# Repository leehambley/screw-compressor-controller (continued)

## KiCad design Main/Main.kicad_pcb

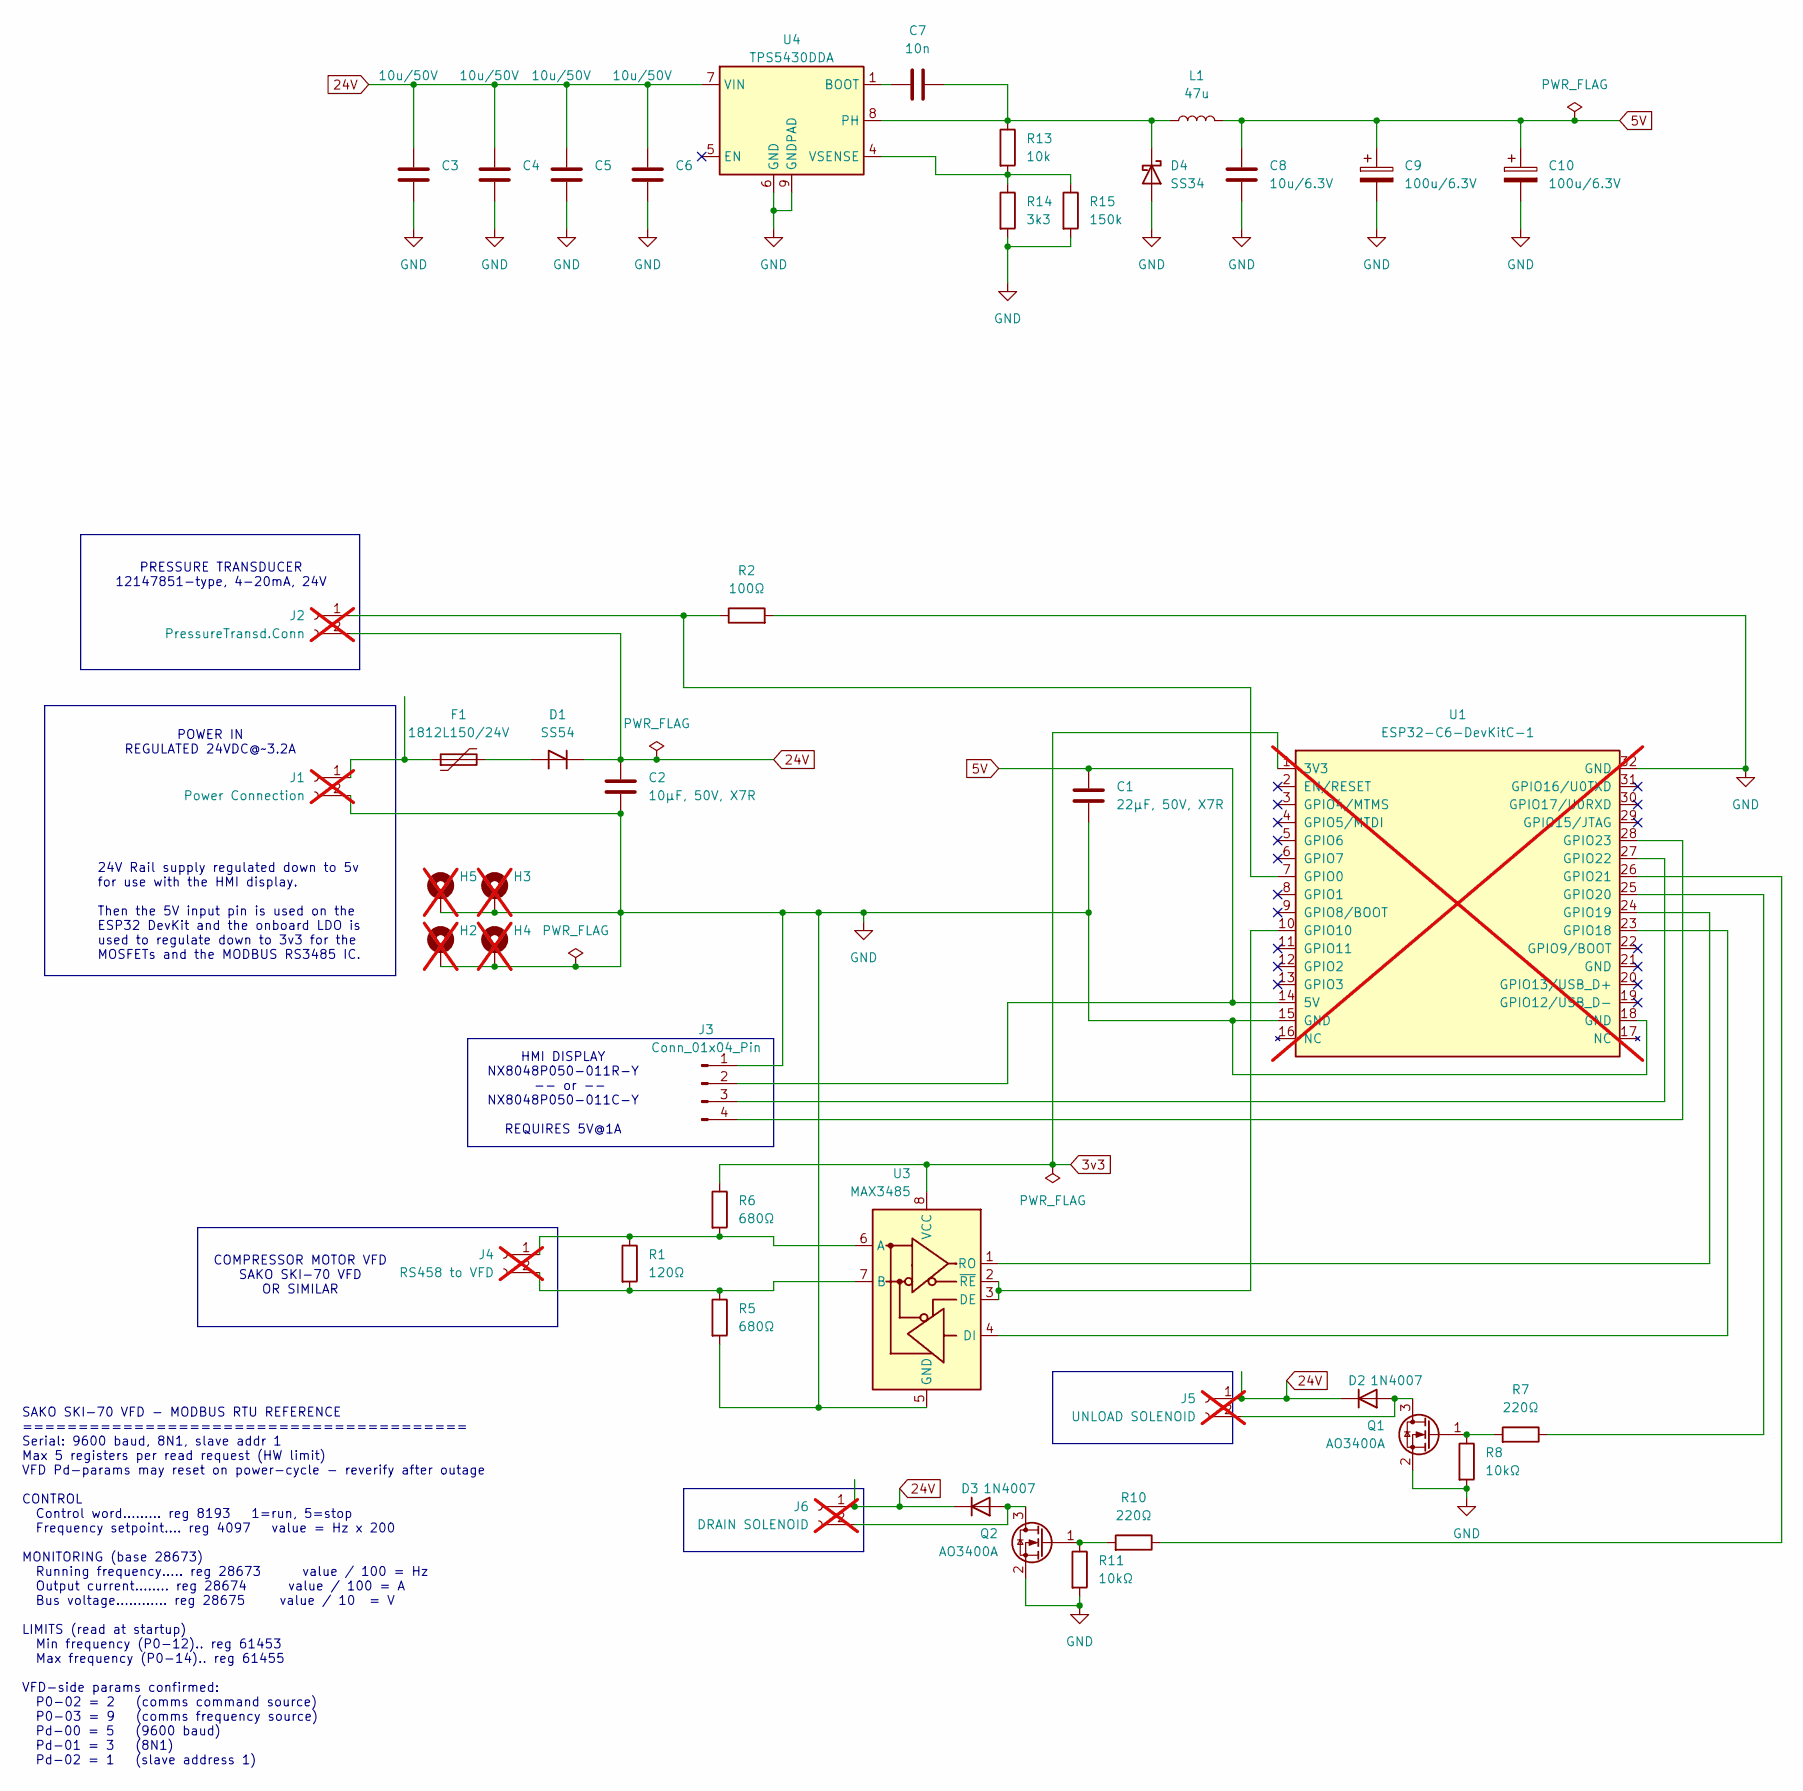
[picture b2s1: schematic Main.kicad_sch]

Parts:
C1: 22µF, 50V, X7R; C_0603_1608Metric; LCSC C14663
C2: 10µF, 50V, X7R; C_1206_3216Metric; LCSC C49326770
C3, C4, C5, C6: 10u/50V; C_1206_3216Metric; MPN CL31A106KBHNNNE; LCSC C13585
C7: 10n; C_0402_1005Metric; MPN CL05B103KB5NNNC; LCSC C15195
C8: 10u/6.3V; C_0402_1005Metric; MPN CL05A106MQ5NUNC; LCSC C15525
C9, C10: 100u/6.3V; CP_EIA-3528-21_Kemet-B; MPN TAJB107K006RNJ; LCSC C16133
D1: SS54; D_SMA; LCSC C22452
D2, D3: 1N4007; D_DO-41_SOD81_P10.16mm_Horizontal; LCSC C84641
D4: SS34; D_SMA; MPN SS34; LCSC C8678
F1: 1812L150/24V; Fuse_1812_4532Metric; LCSC C49318453
H2, H3, H4, H5: MountingHole_Pad_MP; MountingHole_3.2mm_M3_DIN965_Pad; not fitted
J1: Power Connection; TerminalBlock_MaiXu_MX126-5.0-02P_1x02_P5.00mm; LCSC C3703; not fitted
J2: PressureTransd.Conn; TerminalBlock_MaiXu_MX126-5.0-02P_1x02_P5.00mm; LCSC C3703; not fitted
J3: Conn_01x04_Pin; PinHeader_1x04_P2.54mm_Horizontal
J4: RS458 to VFD; TerminalBlock_MaiXu_MX126-5.0-02P_1x02_P5.00mm; LCSC C3703; not fitted
J5: UNLOAD SOLENOID; TerminalBlock_MaiXu_MX126-5.0-02P_1x02_P5.00mm; LCSC C3703; not fitted
J6: DRAIN SOLENOID; TerminalBlock_MaiXu_MX126-5.0-02P_1x02_P5.00mm; LCSC C3703; not fitted
L1: 47u; L_Wuerth_HCM-1190; MPN MWSA1004S-470MT; LCSC C408491
Q1, Q2: AO3400A; SOT-23; LCSC C20917
R1: 120Ω; R_0805_2012Metric; LCSC C17437
R2: 100Ω; R_0805_2012Metric; LCSC C17408
R5, R6: 680Ω; R_0805_2012Metric; LCSC C17798
R7, R10: 220Ω; R_0805_2012Metric; LCSC C17557
R8, R11: 10kΩ; R_0805_2012Metric; LCSC C17414
R13: 10k; R_0402_1005Metric; MPN 0402WGF1002TCE; LCSC C25744
R14: 3k3; R_0402_1005Metric; MPN 0402WGF3301TCE; LCSC C25890
R15: 150k; R_0402_1005Metric; MPN 0402WGF1503TCE; LCSC C25755
U1: ESP32-C6-DevKitC-1; not fitted
U3: MAX3485; SOIC-8_3.9x4.9mm_P1.27mm
U4: TPS5430DDA; TI_SO-PowerPAD-8_ThermalVias; MPN TPS5430DDAR; JLC LSOP-8_EP_3.9x4.9x1.27P

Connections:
3v3: R6.1, U1.1 (3V3), U3.8 (VCC)
5V: C1.1, C8.1, C9.1, C10.1, J3.2, L1.2, U1.14 (5V)
24V: C2.1, C3.1, C4.1, C5.1, C6.1, D1.1 (K), D2.1 (K), D3.1 (K), J2.2, J5.1, J6.1, U4.7 (VIN)
GND: C1.2, C2.2, C3.2, C4.2, C5.2, C6.2, C8.2, C9.2, C10.2, D4.2 (A), H2.MP, H3.MP, H4.MP, H5.MP, J1.2, J3.1, Q1.2 (S), Q2.2 (S), R2.2, R5.2, R8.2, R11.2, R14.2, R15.2, U1.15 (GND), U1.18 (GND), U1.32 (GND), U3.5 (GND), U4.6 (GND), U4.9 (GNDPAD)
unnamed: D1.2 (A), F1.2
unnamed: D2.2 (A), J5.2, Q1.3 (D)
unnamed: D3.2 (A), J6.2, Q2.3 (D)
unnamed: C7.2, D4.1 (K), L1.1, R13.1, U4.8 (PH)
unnamed: F1.1, J1.1
unnamed: J2.1, R2.1, U1.7 (GPIO0)
unnamed: J3.3, U1.27 (GPIO22)
unnamed: J3.4, U1.28 (GPIO23)
unnamed: J4.1, R1.1, R6.2, U3.6 (A)
unnamed: J4.2, R1.2, R5.1, U3.7 (B)
unnamed: Q1.1 (G), R7.2, R8.1
unnamed: Q2.1 (G), R10.2, R11.1
unnamed: U1.10 (GPIO10), U3.2 (~RE), U3.3 (DE)
unnamed: U1.23 (GPIO18), U3.4 (DI)
unnamed: U1.24 (GPIO19), U3.1 (RO)
unnamed: R7.1, U1.25 (GPIO20)
unnamed: R10.1, U1.26 (GPIO21)
unnamed: C7.1, U4.1 (BOOT)
unnamed: R13.2, R14.1, R15.1, U4.4 (VSENSE)

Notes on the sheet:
24V Rail supply regulated down to 5v for use with the HMI display. Then the 5V input pin is used on the ESP32 DevKit and the onboard LDO is used to regulate down to 3v3 for the MOSFETs and the MODBUS RS3485 IC.
HMI DISPLAY NX8048P050-011R-Y -- or -- NX8048P050-011C-Y REQUIRES 5V@1A
POWER IN REGULATED 24VDC@~3.2A
SAKO SKI-70 VFD - MODBUS RTU REFERENCE ======================================== Serial: 9600 baud, 8N1, slave addr 1 Max 5 registers per read request (HW limit) VFD Pd-params may reset on power-cycle - reverify after outage CONTROL Control word......... reg 8193 1=run, 5=stop Frequency setpoint....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
PRESSURE TRANSDUCER 12147851-type, 4-20mA, 24V
COMPRESSOR MOTOR VFD SAKO SKI-70 VFD OR SIMILAR

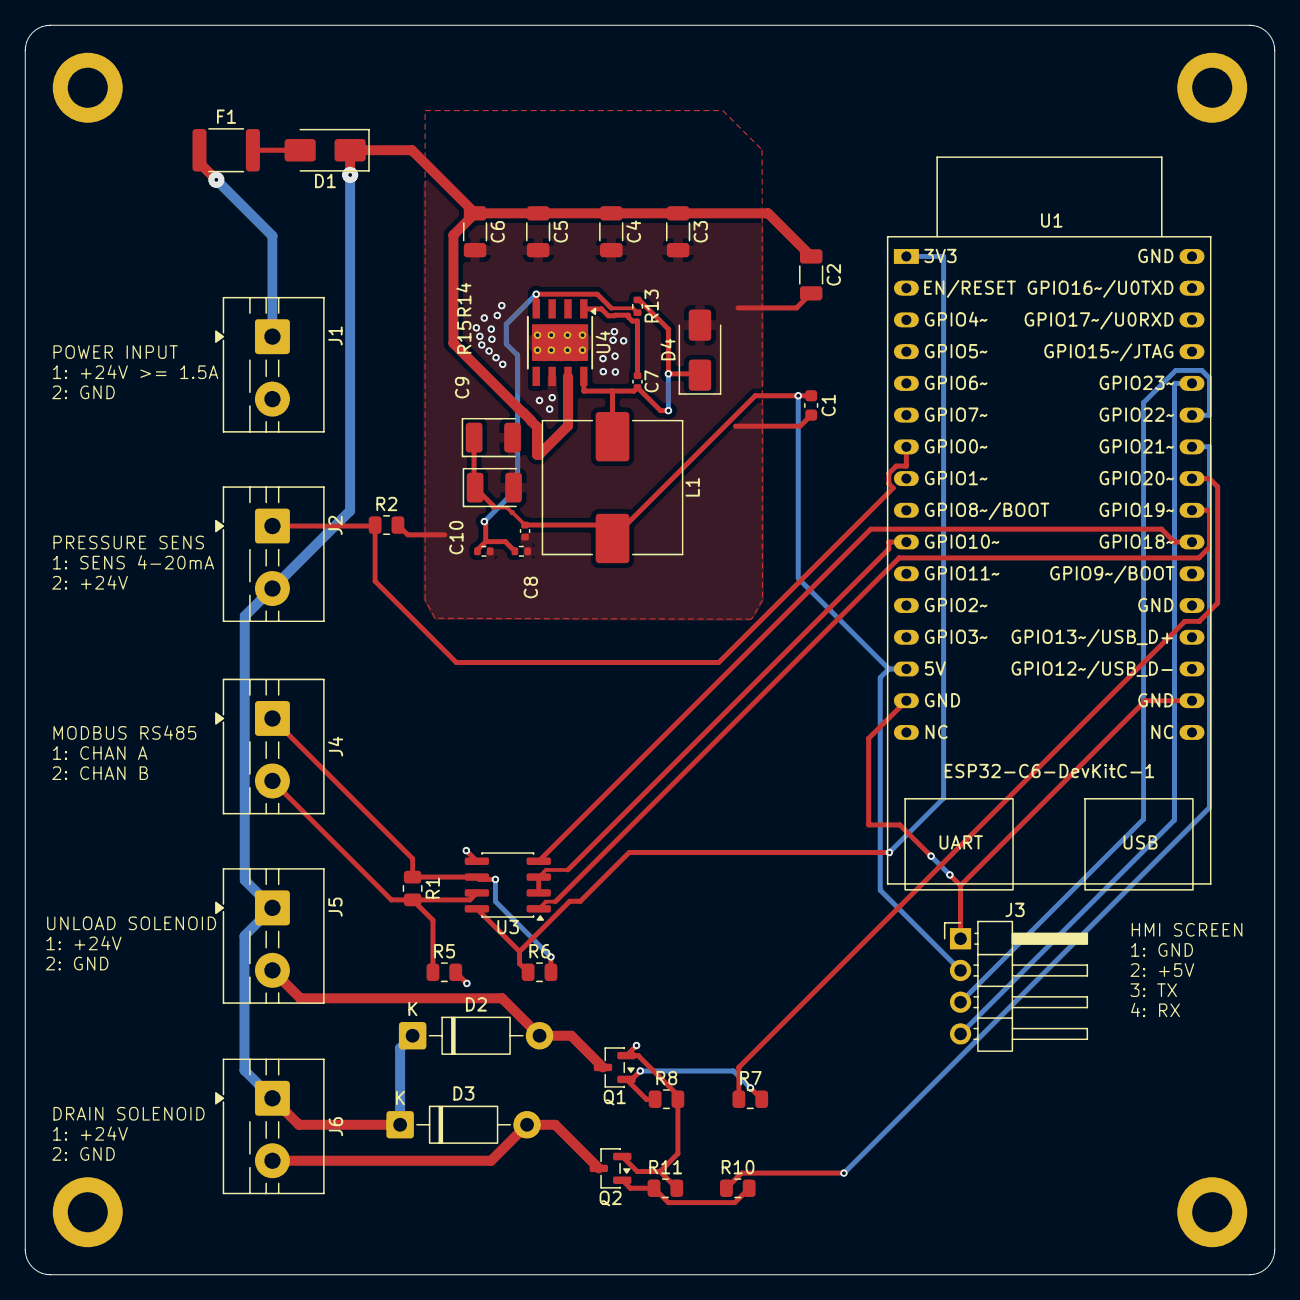
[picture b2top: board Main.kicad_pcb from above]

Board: 2 copper layers, 100.0 x 100.0 mm, 42 parts (0 on the bottom side), 23 nets.

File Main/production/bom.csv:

Designator,Footprint,Quantity,Value,LCSC Part #
C1,0603,1,"22µF, 50V, X7R",C14663
"C10, C9",CP_EIA-3528-21_Kemet-B,2,100u/6.3V,C16133
C2,1206,1,"10µF, 50V, X7R",C49326770
"C3, C4, C5, C6",1206,4,10u/50V,C13585
C7,0402,1,10n,C15195
C8,0402,1,10u/6.3V,C15525
D1,D_SMA,1,SS54,C22452
"D2, D3",D_DO-41_SOD81_P10.16mm_Horizontal,2,1N4007,C84641
D4,D_SMA,1,SS34,C8678
F1,1812,1,1812L150/24V,C49318453
J1,TerminalBlock_MaiXu_MX126-5.0-02P_1x02_P5.00mm,1,Power Connection,C3703
J2,TerminalBlock_MaiXu_MX126-5.0-02P_1x02_P5.00mm,1,PressureTransd.Conn,C3703
J3,PinHeader_1x04_P2.54mm_Horizontal,1,Conn_01x04_Pin,
J4,TerminalBlock_MaiXu_MX126-5.0-02P_1x02_P5.00mm,1,RS458 to VFD,C3703
J5,TerminalBlock_MaiXu_MX126-5.0-02P_1x02_P5.00mm,1,UNLOAD SOLENOID,C3703
J6,TerminalBlock_MaiXu_MX126-5.0-02P_1x02_P5.00mm,1,DRAIN SOLENOID,C3703
L1,L_Wuerth_HCM-1190,1,47u,C408491
"Q1, Q2",SOT-23,2,AO3400A,C20917
R1,0805,1,120Ω,C17437
"R10, R7",0805,2,220Ω,C17557
"R11, R8",0805,2,10kΩ,C17414
R13,0402,1,10k,C25744
R14,0402,1,3k3,C25890
R15,0402,1,150k,C25755
R2,0805,1,100Ω,C17408
"R5, R6",0805,2,680Ω,C17798
U3,SOIC-8_3.9x4.9mm_P1.27mm,1,MAX3485,
U4,TI_SO-PowerPAD-8_ThermalVias,1,TPS5430DDA,C9864

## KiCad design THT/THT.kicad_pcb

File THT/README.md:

# THT controller board (rev A)

A 100 × 100 mm, 2-layer through-hole version of the breadboard controller,
for hand soldering. There is no schematic: [gen_board.py](gen_board.py) declares
every part, position and net, and is the source of truth.

## Ordering (JLCPCB)

Upload `production/THT-gerbers-JLCPCB.zip`. Defaults are fine: 2 layers,
1.6 mm, HASL, 1 oz copper. Parts list: `production/BOM.csv`.

## Rebuilding

```sh
PY=/Applications/KiCad/KiCad.app/Contents/Frameworks/Python.framework/Versions/Current/bin/python3
$PY gen_board.py   # parts + nets, unrouted
$PY route.py       # Freerouting (needs Homebrew openjdk@25) + GND pours
```

Then re-export:

```sh
K=/Applications/KiCad/KiCad.app/Contents/MacOS/kicad-cli
rm -rf production/gerbers && mkdir -p production/gerbers
$K pcb drc -o build/drc.txt THT.kicad_pcb
$K pcb export gerbers --layers F.Cu,B.Cu,F.SilkS,B.SilkS,F.Mask,B.Mask,Edge.Cuts --no-protel-ext -o production/gerbers/ THT.kicad_pcb
$K pcb export drill --format excellon --excellon-separate-th -o production/gerbers/ THT.kicad_pcb
(cd production/gerbers && rm -f ../THT-gerbers-JLCPCB.zip && zip -q ../THT-gerbers-JLCPCB.zip *)
```

## Circuit

| Block | Parts | Notes |
|---|---|---|
| 24 V in | J1, F1 (2 A slow 5×20), D1 1N5822, C1, C2 | D1 = reverse-polarity protection |
| 5 V | U2 LM2596T-5.0, L1 33 µH, D2 1N5822, C3, C4 | feeds Nextion directly, DevKit 5V pin via D3 1N5819 (no back-feed into USB) |
| 3V3 | DevKit's own regulator | MAX3485, NTC pull-ups, ADC clamp |
| Valve 1 (start-assist, GPIO20) | Q1 IRLZ34N, R10 100R gate, R12 100k pull-down, D4 1N5819, LED2 | |
| Valve 2 (drain, GPIO21) | Q2, R11, R13, D5, LED3 | |
| Pressure 4–20 mA (GPIO0) | J4, R20 100R shunt, R21 1k + C20 100nF, D20 BAT85 clamp | J4: top = +24 V loop supply, bottom = signal |
| NTC1 rotor (GPIO1), NTC2 motor (GPIO2), NTC3 rotor 2 (GPIO3) | 10k pull-up, 1k + 100nF each | probes are non-polar |
| RS485 (GPIO18 DI, GPIO19 RO, GPIO10 DE/RE) | U3 MAX3485 (DIP-8, socketed), R40 120R via JP1, R42 10k RO pull-up | J8: A, B, GND |
| Nextion (GPIO22 RX, GPIO23 TX) | J9 JST XH 4-pin (B4B-XH-A): 5V, TX, RX, GND | same connector and pin order as the display end |

Bottom layer is an almost unbroken ground plane, top is ground-poured too.
Valve current returns along the right-hand side to J1; the analog front
end is on the far left, away from it. That is the lesson from the
breadboard, whose readings were wrecked by a shared, poorly soldered ground.

Flyback diodes are Schottky (1N5819), so the valve PWM hold can go well
above 1 kHz (quiet) without the 1N400x reverse-recovery heating.

## Check before ordering parts

- F1 clips: footprint is Littelfuse 100-series clips, 20.5 mm pitch. Buy
  matching clips or swap the footprint for your holder.
- L1: 12 mm radial, 5 mm lead pitch, ≥ 1.5 A.
- U2: footprint is for the staggered-lead TO-220-5 (LM2596T-5.0 /
  "flow LB03"); straight-lead parts can be bent to fit.
- DevKit goes in 2× 1x16 female headers; its USB ports overhang the bottom
  edge so it can still be flashed in place.

## Firmware follow-ups

- NTC2 (GPIO2) and NTC3 (GPIO3) are new; the firmware only reads GPIO1.

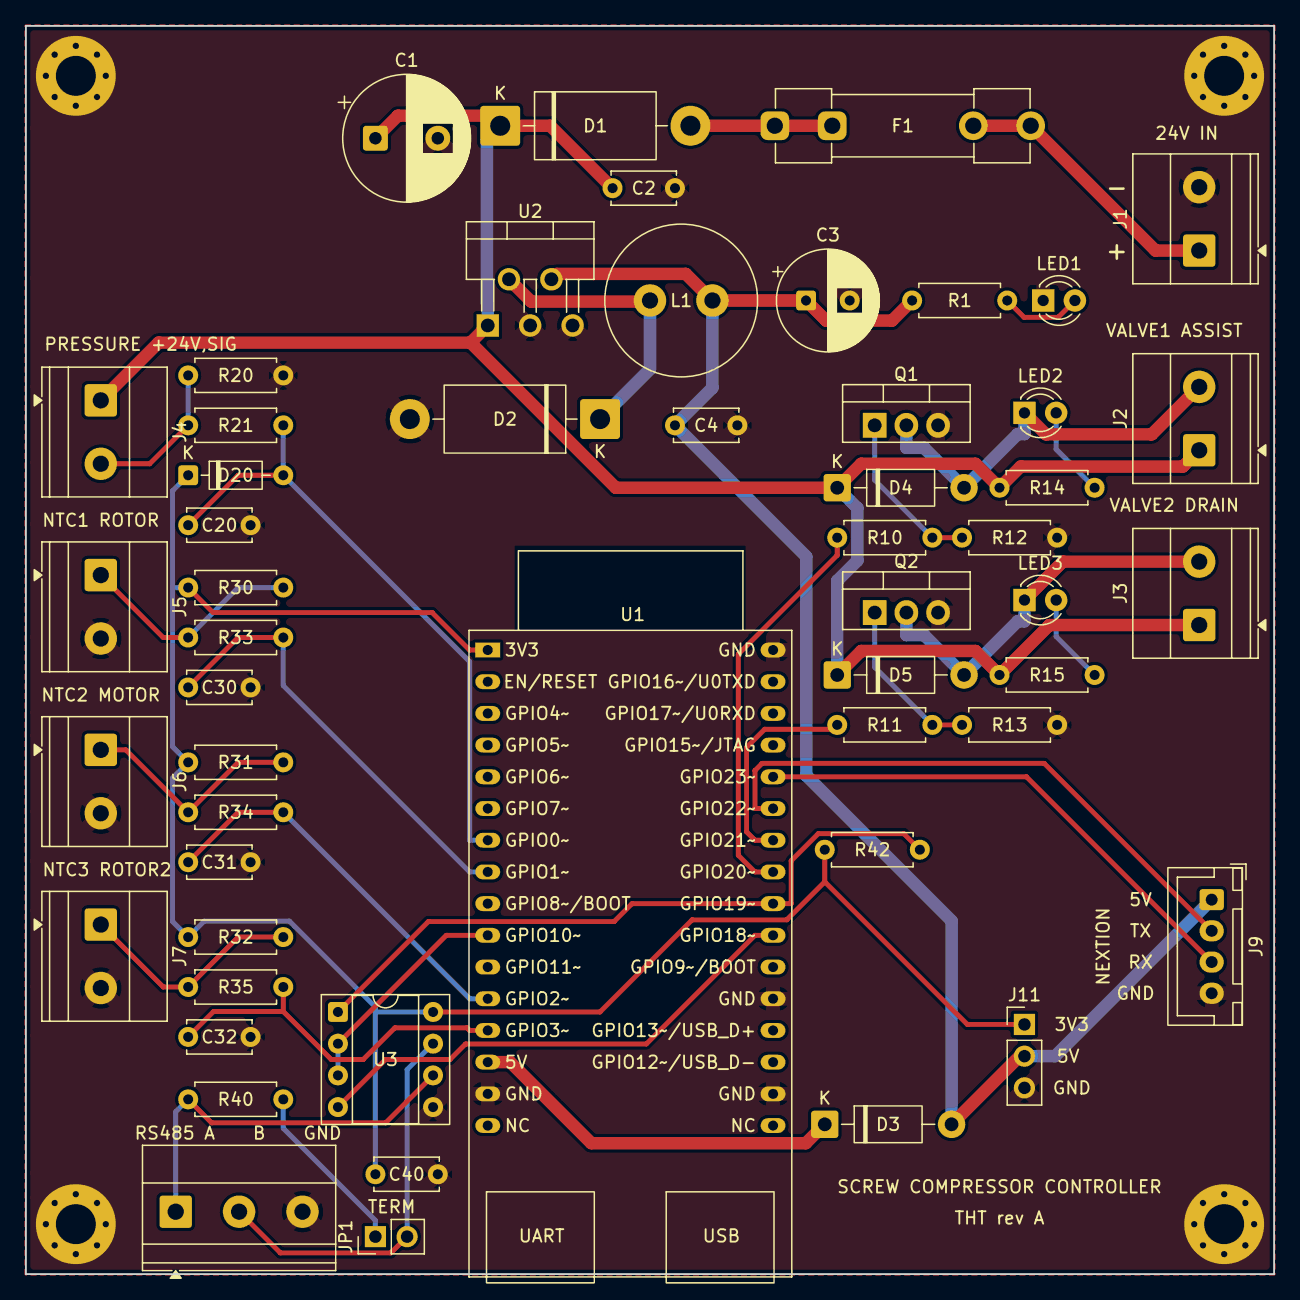
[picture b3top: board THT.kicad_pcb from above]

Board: 2 copper layers, 100.0 x 100.0 mm, 57 parts (0 on the bottom side), 33 nets.

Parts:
C1: 220uF 50V; CP_Radial_D10.0mm_P5.00mm
C2: 100nF 50V; C_Disc_D5.0mm_W2.5mm_P5.00mm
C3: 220uF 25V low-ESR; CP_Radial_D8.0mm_P3.50mm
C4, C20, C30, C31, C32, C40: 100nF; C_Disc_D5.0mm_W2.5mm_P5.00mm
D1, D2: 1N5822; D_DO-201AD_P15.24mm_Horizontal
D3, D4, D5: 1N5819; D_DO-41_SOD81_P10.16mm_Horizontal
D20: BAT85; D_DO-35_SOD27_P7.62mm_Horizontal
F1: 2A slow 5x20; Fuseholder_Clip-5x20mm_Littelfuse_100_Inline_P20.50x4.60mm_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
H1, H2, H3, H4: M3; MountingHole_3.2mm_M3_Pad_Via
J1: 24V IN; TerminalBlock_Phoenix_MKDS-1,5-2-5.08_1x02_P5.08mm_Horizont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
J2: VALVE1; TerminalBlock_Phoenix_MKDS-1,5-2-5.08_1x02_P5.08mm_Horizont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
J3: VALVE2; TerminalBlock_Phoenix_MKDS-1,5-2-5.08_1x02_P5.08mm_Horizont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
J4: PRESSURE; TerminalBlock_Phoenix_MKDS-1,5-2-5.08_1x02_P5.08mm_Horizont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
J5: NTC1; TerminalBlock_Phoenix_MKDS-1,5-2-5.08_1x02_P5.08mm_Horizont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
J6: NTC2; TerminalBlock_Phoenix_MKDS-1,5-2-5.08_1x02_P5.08mm_Horizont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
J7: NTC3; TerminalBlock_Phoenix_MKDS-1,5-2-5.08_1x02_P5.08mm_Horizont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
J8: RS485; TerminalBlock_Phoenix_MKDS-1,5-3-5.08_1x03_P5.08mm_Horizont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
J9: JST XH 4P (B4B-XH-A); JST_XH_B4B-XH-A_1x04_P2.50mm_Vertical
J11: TEST; PinHeader_1x03_P2.54mm_Vertical
JP1: TERM; PinHeader_1x02_P2.54mm_Vertical
L1: 33uH 3A; L_Radial_D12.0mm_P5.00mm_Fastron_11P
LED1: green 3mm; LED_D3.0mm
LED2, LED3: red 3mm; LED_D3.0mm
Q1, Q2: IRLZ34N; TO-220-3_Vertical
R1, R21, R33, R34, R35: 1k; R_Axial_DIN0207_L6.3mm_D2.5mm_P7.62mm_Horizontal
R10, R11: 100R; R_Axial_DIN0207_L6.3mm_D2.5mm_P7.62mm_Horizontal
R12, R13: 100k; R_Axial_DIN0207_L6.3mm_D2.5mm_P7.62mm_Horizontal
R14, R15: 4k7; R_Axial_DIN0207_L6.3mm_D2.5mm_P7.62mm_Horizontal
R20: 100R 1%; R_Axial_DIN0207_L6.3mm_D2.5mm_P7.62mm_Horizontal
R30, R31, R32: 10k 1%; R_Axial_DIN0207_L6.3mm_D2.5mm_P7.62mm_Horizontal
R40: 120R; R_Axial_DIN0207_L6.3mm_D2.5mm_P7.62mm_Horizontal
R42: 10k; R_Axial_DIN0207_L6.3mm_D2.5mm_P7.62mm_Horizontal
U1: ESP32-C6-DevKitC-1
U2: LM2596T-5.0; TO-220-5_P3.4x3.7mm_StaggerOdd_Lead3.8mm_Vertical
U3: MAX3485CPA; DIP-8_W7.62mm_Socket

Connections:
5V_DK: D3.1, U1.14
+3V3: C40.1, D20.1, J11.1, R30.1, R31.1, R32.1, R42.1, U1.1, U3.8
+5V: C3.1, C4.1, D3.2, J9.1, J11.2, L1.2, R1.1, U2.4
+24V: C1.1, C2.1, D1.1, D4.1, D5.1, J2.1, J3.1, J4.1, R14.1, R15.1, U2.1
ADC0: C20.1, D20.2, R21.2, U1.7
ADC1: C30.1, R33.2, U1.8
ADC2: C31.1, R34.2, U1.12
ADC3: C32.1, R35.2, U1.13
DRAIN1: D4.2, J2.2, LED2.1, Q1.2
DRAIN2: D5.2, J3.2, LED3.1, Q2.2
G1: Q1.1, R10.2, R12.1
G2: Q2.1, R11.2, R13.1
GND: C1.2, C2.2, C3.2, C4.2, C20.2, C30.2, C31.2, C32.2, C40.2, D2.2, H1.1, H2.1, H3.1, H4.1, J1.2, J5.2, J6.2, J7.2, J8.3, J9.4, J11.3, LED1.1, Q1.3, Q2.3, R12.2, R13.2, R20.2, U1.15, U1.18, U1.21, U1.32, U2.3, U2.5, U3.5
LED_PWR: LED1.2, R1.2
LED_V1: LED2.2, R14.2
LED_V2: LED3.2, R15.2
LOOP: J4.2, R20.1, R21.1
MB_DE: U1.10, U3.2, U3.3
MB_DI: U1.23, U3.4
MB_RO: R42.2, U1.24, U3.1
NEX_RX: J9.3, U1.28
NEX_TX: J9.2, U1.27
NTC1: J5.1, R30.2, R33.1
NTC2: J6.1, R31.2, R34.1
NTC3: J7.1, R32.2, R35.1
RS_A: J8.1, R40.1, U3.6
RS_B: J8.2, JP1.2, U3.7
SW: D2.1, L1.1, U2.2
TERM: JP1.1, R40.2
V1_IN: R10.1, U1.25
V2_IN: R11.1, U1.26
VIN_F: D1.2, F1.1
VIN_RAW: F1.2, J1.1

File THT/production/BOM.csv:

Qty,References,Value,Footprint
1,C1,220uF 50V,CP_Radial_D10.0mm_P5.00mm
1,C2,100nF 50V,C_Disc_D5.0mm_W2.5mm_P5.00mm
1,C3,220uF 25V low-ESR,CP_Radial_D8.0mm_P3.50mm
6,C4 C20 C30 C31 C32 C40,100nF,C_Disc_D5.0mm_W2.5mm_P5.00mm
2,D1 D2,1N5822,D_DO-201AD_P15.24mm_Horizontal
3,D3 D4 D5,1N5819,D_DO-41_SOD81_P10.16mm_Horizontal
1,D20,BAT85,D_DO-35_SOD27_P7.62mm_Horizontal
1,F1,2A slow 5x20,Fuseholder_Clip-5x20mm_Littelfuse_100_Inline_P20.50x4.60mm_D1.30mm_Horizontal
1,J1,24V IN,"TerminalBlock_Phoenix_MKDS-1,5-2-5.08_1x02_P5.08mm_Horizontal"
1,J2,VALVE1,"TerminalBlock_Phoenix_MKDS-1,5-2-5.08_1x02_P5.08mm_Horizontal"
1,J3,VALVE2,"TerminalBlock_Phoenix_MKDS-1,5-2-5.08_1x02_P5.08mm_Horizontal"
1,J4,PRESSURE,"TerminalBlock_Phoenix_MKDS-1,5-2-5.08_1x02_P5.08mm_Horizontal"
1,J5,NTC1,"TerminalBlock_Phoenix_MKDS-1,5-2-5.08_1x02_P5.08mm_Horizontal"
1,J6,NTC2,"TerminalBlock_Phoenix_MKDS-1,5-2-5.08_1x02_P5.08mm_Horizontal"
1,J7,NTC3,"TerminalBlock_Phoenix_MKDS-1,5-2-5.08_1x02_P5.08mm_Horizontal"
1,J8,RS485,"TerminalBlock_Phoenix_MKDS-1,5-3-5.08_1x03_P5.08mm_Horizontal"
1,J9,JST XH 4P (B4B-XH-A),JST_XH_B4B-XH-A_1x04_P2.50mm_Vertical
1,J11,TEST,PinHeader_1x03_P2.54mm_Vertical
1,JP1,TERM,PinHeader_1x02_P2.54mm_Vertical
1,L1,33uH 3A,L_Radial_D12.0mm_P5.00mm_Fastron_11P
1,LED1,green 3mm,LED_D3.0mm
2,LED2 LED3,red 3mm,LED_D3.0mm
2,Q1 Q2,IRLZ34N,TO-220-3_Vertical
5,R1 R21 R33 R34 R35,1k,R_Axial_DIN0207_L6.3mm_D2.5mm_P7.62mm_Horizontal
2,R10 R11,100R,R_Axial_DIN0207_L6.3mm_D2.5mm_P7.62mm_Horizontal
2,R12 R13,100k,R_Axial_DIN0207_L6.3mm_D2.5mm_P7.62mm_Horizontal
2,R14 R15,4k7,R_Axial_DIN0207_L6.3mm_D2.5mm_P7.62mm_Horizontal
1,R20,100R 1%,R_Axial_DIN0207_L6.3mm_D2.5mm_P7.62mm_Horizontal
3,R30 R31 R32,10k 1%,R_Axial_DIN0207_L6.3mm_D2.5mm_P7.62mm_Horizontal
1,R40,120R,R_Axial_DIN0207_L6.3mm_D2.5mm_P7.62mm_Horizontal
1,R42,10k,R_Axial_DIN0207_L6.3mm_D2.5mm_P7.62mm_Horizontal
1,U1,ESP32-C6-DevKitC-1,ESP32-C6-DevKitC-1
1,U2,LM2596T-5.0,TO-220-5_P3.4x3.7mm_StaggerOdd_Lead3.8mm_Vertical
1,U3,MAX3485CPA,DIP-8_W7.62mm_Socket
2,U1 (socket),1x16 female header 2.54mm,for the DevKit
1,U3 (socket),DIP-8 IC socket,for the MAX3485
1,JP1 (jumper),2.54mm jumper cap,fit = 120R termination on
1,F1 (fuse),2A slow-blow 5x20mm glass fuse,goes in F1's clips

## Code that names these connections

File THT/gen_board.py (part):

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  DevKit 3V3 pin -> MAX3485, NTC pull-ups, ADC clamp
  2x IRLZ34N low-side valve drivers, 1N5819 Schottky flyback (fast enough
    for PWM hold well above 1 kHz), LED per valve
  4-20mA pressure: 100R shunt -> 1k/100nF -> GPIO0, BAT85 clamp to 3V3
  3x NTC: 10k pull-up, 1k/100nF -> GPIO1/2/3
  RS485: MAX3485 DIP-8, 120R termination via jumper
"""
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    # Diode keeps board 5V and USB VBUS from back-feeding each other.
    ("D3", DO41, "1N5819", 64, 88, 0, {"1": "5V_DK", "2": "+5V"}),

    # --- Valve 1: start-assist (GPIO20)
    ("J2", TERM2, "VALVE1", 94, 34, RIGHT, {"1": "+24V", "2": "DRAIN1"}),
    ("Q1", TO220, "IRLZ34N", 68, 32, 0, {"1": "G1", "2": "DRAIN1", "3": "GND"}),
    ("D4", DO41, "1N5819", 65, 37, 0, {"1": "+24V", "2": "DRAIN1"}),
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    ("R14", RES, "4k7", 78, 37, 0, {"1": "+24V", "2": "LED_V1"}),
    ("LED2", LED, "red 3mm", 80, 31, 0, {"1": "DRAIN1", "2": "LED_V1"}),

    # --- Valve 2: drain (GPIO21)
    ("J3", TERM2, "VALVE2", 94, 48, RIGHT, {"1": "+24V", "2": "DRAIN2"}),
    ("Q2", TO220, "IRLZ34N", 68, 47, 0, {"1": "G2", "2": "DRAIN2", "3": "GND"}),
    ("D5", DO41, "1N5819", 65, 52, 0, {"1": "+24V", "2": "DRAIN2"}),
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    ("R15", RES, "4k7", 78, 52, 0, {"1": "+24V", "2": "LED_V2"}),
    ("LED3", LED, "red 3mm", 80, 46, 0, {"1": "DRAIN2", "2": "LED_V2"}),

    # --- Pressure 4-20mA (GPIO0)
    ("J4", TERM2, "PRESSURE", 6, 30, LEFT, {"1": "+24V", "2": "LOOP"}),
    ("R20", RES, "100R 1%", 13, 28, 0, {"1": "LOOP", "2": "GND"}),
    ("R21", RES, "1k", 13, 32, 0, {"1": "LOOP", "2": "ADC0"}),
    ("D20", DO35, "BAT85", 13, 36, 0, {"1": "+3V3", "2": "ADC0"}),
    ("C20", CDISC, "100nF", 13, 40, 0, {"1": "ADC0", "2": "GND"}),

    # --- NTC1 rotor primary (GPIO1)
    ("J5", TERM2, "NTC1", 6, 44, LEFT, {"1": "NTC1", "2": "GND"}),
    ("R30", RES, "10k 1%", 13, 45, 0, {"1": "+3V3", "2": "NTC1"}),
    ("R33", RES, "1k", 13, 49, 0, {"1": "NTC1", "2": "ADC1"}),
    ("C30", CDISC, "100nF", 13, 53, 0, {"1": "ADC1", "2": "GND"}),

    # --- NTC2 motor winding (GPIO2)
    ("J6", TERM2, "NTC2", 6, 58, LEFT, {"1": "NTC2", "2": "GND"}),
    ("R31", RES, "10k 1%", 13, 59, 0, {"1": "+3V3", "2": "NTC2"}),
    ("R34", RES, "1k", 13, 63, 0, {"1": "NTC2", "2": "ADC2"}),
    ("C31", CDISC, "100nF", 13, 67, 0, {"1": "ADC2", "2": "GND"}),

    # --- NTC3 rotor secondary (GPIO3)
    ("J7", TERM2, "NTC3", 6, 72, LEFT, {"1": "NTC3", "2": "GND"}),
    ("R32", RES, "10k 1%", 13, 73, 0, {"1": "+3V3", "2": "NTC3"}),
    ("R35", RES, "1k", 13, 77, 0, {"1": "NTC3", "2": "ADC3"}),
    ("C32", CDISC, "100nF", 13, 81, 0, {"1": "ADC3", "2": "GND"}),

    # --- RS485 (MAX3485, DE+/RE on GPIO10)
    ("U3", "Package_DIP:DIP-8_W7.62mm_Socket", "MAX3485CPA", 25, 79, 0, {
        "1": "MB_RO", "2": "MB_DE", "3": "MB_DE", "4": "MB_DI",
        "5": "GND", "6": "RS_A", "7": "RS_B", "8": "+3V3",
    }),
    ("C40", CDISC, "100nF", 28, 92, 0, {"1": "+3V3", "2": "GND"}),
    ("R40", RES, "120R", 13, 86, 0, {"1": "RS_A", "2": "TERM"}),
    ("JP1", "Connector_PinHeader_2.54mm:PinHeader_1x02_P2.54mm_Vertical", "TERM", 28, 97, 90,
     {"1": "TERM", "2": "RS_B"}),
    ("R42", RES, "10k", 64, 66, 0, {"1": "+3V3", "2": "MB_RO"}),
    ("J8", TERM3, "RS485", 12, 95, DOWN, {"1": "RS_A", "2": "RS_B", "3": "GND"}),
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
